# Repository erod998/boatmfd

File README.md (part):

# Boat Dashboard — Proof of Concept

A DIY Garmin-style MFD for a 7" 16:9 landscape display, restyled after the
look of Garmin's GPSMAP touchscreen chartplotters (near-black panes, round
segmented dials that fill blue, outlined data boxes, a black menu bar with a
Home button) and built for big touch targets while driving the boat.

**Moving to real hardware?** [HARDWARE.md](HARDWARE.md) has the parts list, a picked depth
transducer, and a step-by-step order to bring it up on the boat.

**Screens** (tap **Home** on the menu bar, or the small thumbnails either side
of it, to switch):

| Screen | What it shows |
| --- | --- |
| **Helm** (default) | Everything at once: GPS speed and RPM dials plus coolant / oil / battery / fuel (with estimated GPH and MPG) / trim bars on top, the chart with big Depth and Water Temp boxes in the middle, and trip, Fusion stereo and RGB lights below |
| **Nav. Chart** | Full-screen chart with Speed / Heading / Depth / Water Temp data boxes, zoom buttons, the boat, its heading line and track, an optional compass rose, and waypoint navigation |
| **Gauges** | Garmin-style engine and vessel dials: coolant, oil, battery, fuel, trim, RPM, GPS speed, fuel flow, plus fuel economy / remaining / water temp boxes |
| **Trip** | Start/stop trip logging: distance, time, average and max speed, fuel used and economy, and the saved-trip list |
| **Media** | Fusion stereo over NMEA 2000: cover art, source chips, big transport buttons, a Master volume that moves every zone together (keeping their relative mix), and a volume bar for each zone (with its own mute), plus a mute for everything, plus a gear icon for RPM Volume Boost |
| **RGB Lights** | Twelve colour presets, rainbow, power, and a segmented brightness bar |
| **Switching** | A grid of simulated digital-switching circuits (nav lights, anchor light, cabin lights, livewell, bilge pump, two accessories, horn) — no real switching module, just remembers on/off |

**Also reachable from Options** (not full screens, but full features): **Waypoints, Routes &
Boundaries** (mark/save/rename/delete waypoints, search saved waypoints by name and go straight
to one — like a GPS — build and follow multi-leg routes, circular geofence alarms), **Navigation
Alarms** (Arrival, Off Course, Anchor Drag, GPS Accuracy), and **Pinned Screens** (choose which screens
show in the Home overlay's Pinned tab and the prev/next swipe at the bottom of every screen — at
least one has to stay pinned).

**Home** is a translucent overlay like Garmin's: a clock (tap **Home** any time to check
it), a row of screen thumbnails above category tabs (Pinned, Charts, Combo, Vessel, Media,
Lights). The menu bar also has **Mark** (drop a waypoint at the boat), **Info** (data sources,
position, GPS status), **Day/Night** chart mode, **Alerts** (the alarms and
warnings below, and a missing GPS fix; the icon turns amber/red with a count)
and **Options** (units, alarms, chart orientation, map layers & colors, centre chart on
boat, waypoints, calibration). Tap the speed gauge to switch between mph and knots. The
chart defaults to **Old Hickory Lake, TN (37075)**, and has the three orientations a GPSMAP
does: **North Up** (default), **Heading Up** (the bow points to the top of the screen) and
**Course Up** (the *active leg* points to the top). Course Up is the one worth knowing about —
Heading Up re-aims the chart with every wiggle of the boat, which at idle is a constant slow
swim, while Course Up holds the leg still and lets the boat icon swing against it, so the angle
between the icon and straight-up is exactly how much you are crabbing off the track. With no Go
To or route running it falls back to course over ground, then heading, so it is never stuck
pointing somewhere stale. The chart button beside the zoom controls is labelled with the current
mode (**N↑**, **H↑**, **C↑**) and switches in one press between North Up and whichever rotating
mode you last chose; **Options → Chart orientation** cycles through all three. (It used to cycle
all three itself, and since Heading Up and Course Up look alike on a straight run, getting back
to North Up took two presses.)

**Following the boat**: the chart keeps the boat centred (North Up) or a third of the way up the
screen (Heading and Course Up) until you drag it. Then it stays where you put it, and a blue
**Center** button appears above the ruler; tap it to go back to the boat. Pinching or the +/−
buttons zoom without letting go of the boat.

**The chart cursor** — what a tap on the chart does, the way a GPSMAP does it: it drops a cursor
and does nothing else yet. The bar that appears says how far away it is and in which direction,
its position, and what is charted there (the depth band, or a bridge, dam or caution area — tap
that line for the full details); **Go To** navigates there, **Save Waypoint** keeps it. A tap used
to start a Go To immediately, and since a Go To and a route are mutually exclusive, one stray tap
in a chop cancelled an active route. Tapping an aid to navigation, mile marker, landmark or
hazard point identifies it instead, with its own Go To. Only those point features take a tap;
land, depth areas and shorelines used to as well, which between them cover the whole chart, so
every tap opened "Land" and the chart could not be tapped for anything else at all.

**Go To follows the channel** (auto guidance): a Go To is planned over the water, preferring the
Corps' recommended track down the channel, and leaves it only to reach a destination off it -- up a
creek, into a marina. The route is drawn as a dashed line and steered leg by leg: bearing, course
and cross-track error are for the current leg (so Course Up turns with the channel), distance and
time to go are along the rest of the route. With no chart or no way through the water it falls
back to a straight line and says so. Saved routes (Route To) still run straight between their
waypoints, as they do on a GPSMAP.

**Look-ahead**: in North Up the boat sits a third of the way in from the edge it is coming from,
so two thirds of the screen is the water ahead -- the bottom third heading north, the left third
heading east. It follows the course over the ground above 2 kn.

**Measure Distance** (the ruler button beside the zoom controls): the reference starts at the
boat and follows it; each tap on the chart moves the far end, and the range and bearing read out
at the top of the chart. **Set Ref** pins the reference to that point instead, to measure between
two arbitrary points; **From Boat** puts it back. (Built for a finger: an earlier version relied on
mouse hover and read 0.00 on a touchscreen.)

**Range Rings** (**Options → Map layers & colors → My Vessel**): four concentric circles around
the boat at a spacing you pick, the outermost labelled with its radius, so distance to anything
on screen can be eyeballed without measuring it. Drawn in real distance rather than screen
pixels, so they scale with zoom the way the chart does.

The boat's position and heading are eased continuously (every animation frame, not once a
second when a GPS fix arrives) — the same idea as the spring-smoothed gauges, but for a
wrapped compass angle and a lat/lon position: `setBoatTarget()`/`boatTick()` in app.js. This
drives the boat icon, the chart's own bearing in Heading Up (which turns the whole chart so
the boat's current heading points to the top of the screen, the boat icon then always
pointing straight up), and the position lock that keeps the boat horizontally centered and
about a third of the way up from the bottom of the map in Heading Up — a single cheap
`panBy` every frame, not a `setView`, so it holds through the whole rotation instead of only
correcting once a second. The chart itself is vector data held in memory (see **Charts**), so
panning and rotating never wait on anything to load and never show a blank square — the old
raster-tile black-square problem went away with the tiles.

**Map layers & colors** (**Options → Map layers & colors**, or the app/gps.py and
app/state.py simulators' more realistic noise): chart colors are Day/Dusk/Night — three real
palettes applied to the chart vectors themselves, not a filter smeared over an image, so the
boat and track keep their own colours while only the chart changes;
**Chart** layer toggles (Land & shoreline, Depths & contours, Aids to navigation, Hazards &
caution areas, Landmarks) add and remove the matching vector layers on the spot, with no
refetching — the data is already local; **My Vessel** has a Heading Line
(projects ahead of the boat by a fixed distance or by how far it'll travel in a set time at
its current speed — Distance/Time, matching a real GPSMAP's own Heading Line options) and a
Compass Rose (a fixed-size ring around the boat marked N/E/S/W — left un-rotated in CSS on
purpose, since leaflet-rotate spins the whole marker pane with the chart, the same reason the
boat icon has to counter-rotate to stay pointing up in Heading Up); **User Data** can hide the
recorded track, clear it, name and **save** the current breadcrumb trail as a permanent record
(kept in `data/tracks.json`, up to the same ~600-point/~10-minute window the live trail itself
keeps — a real chartplotter's active-track memory has the same kind of limit), and lists every
saved track — tap one to draw it on the chart in green, tap again to hide it, tap the pencil to
rename it in place, tap the arrow to drop a waypoint back at its starting point (retracing it, the
way you'd want to find your way back to the dock after an out-and-back cruise), or delete it. All
of this is a per-browser preference (localStorage) except clearing the track, and saved tracks
themselves, which live on the server (`/api/track`, `/api/tracks`).

**Data overlays** (the Speed/Heading/Depth/... boxes on the Helm and Nav. Chart screens): **hold**
any box (same gesture, and the same fill-as-you-hold feedback, as the RPM display and alarm
menus) to swap in a different field, matching a real GPSMAP's "Edit Overlays". There are **36
fields in seven groups**, and the picker shows the group headings because a flat list of that
many is not something anyone navigates while driving:

| Group | Fields |
| --- | --- |
| **Navigation** | Bearing, Course, Distance, Time To Dest, Arrival Time, VMG, Cross Track, Turn, Destination |
| **Vessel** | Speed, Heading, Course Over Ground, Position, GPS Accuracy, Satellites |
| **Depth & Water** | Depth, Water Temp |
| **Engine** | RPM, Engine Temp, Oil Pressure, Trim, Battery |
| **Fuel** | Fuel Level, Fuel Remaining, Fuel Rate, Fuel Economy, Range |
| **Trip** | Trip Distance, Trip Time, Average Speed, Max Speed, Trip Fuel Used |
| **Time** | Time of Day, Sunrise, Sunset, Moon Phase |

The Navigation group needs a Go To or a route running and reads `--` otherwise, the Trip group
needs a trip started, and everything reads `--` without a GPS fix — which is what a real unit
does rather than showing a stale or invented number. **VMG** is velocity made good: how fast the
distance to the destination is actually shrinking, which is only the same as speed when steering
straight at it. **Time To Dest** is computed from VMG rather than speed for exactly that reason
— sliding sideways past a waypoint at 20 kn is not arriving at 20 kn — and reads `--` when VMG
has gone negative, because a boat pointed away is not arriving at all. **Fuel Remaining**,
**Economy** and **Range** need the tank size (`BOAT_FUEL_CAPACITY_GAL`, default 40).
Which fields are picked, per screen, is a per-browser preference (localStorage);
the Chart screen defaults to Speed/Heading/Depth/Water Temp and the Helm screen (which already
shows speed via its own dial) to Depth/Water Temp, same as before this was made editable.
Sunrise, sunset and moon phase come from `app/celestial.py` — sunrise/sunset from the standard
astronomical "sunrise equation" using the boat's own position, moon phase from the days elapsed
since a known new moon (the same for every observer, so it only needs a date) — both accurate to
civil (not celestial-navigation) precision, no network call or API key, and (deliberately) not
tide/current predictions or moonrise/moonset times, which either wouldn't mean anything on a
freshwater lake (tide/current) or need meaningfully more work to compute well (the moon's real
position, not just its phase angle) than this dashboard's use case calls for.

**Alarms:** hold your finger on a gauge for about half a second (the gauge
fills as you hold) to open its alarm menu: coolant / engine temperature, oil
pressure, battery voltage (a low and a high alarm), fuel level, or the Depth
box. **Options → Alarms** lists them all. Each has an on/off switch and a
level you set with the big −/+ buttons or by tapping the bar; a small bell
marks every gauge that has an alarm on, and the gauge's red and amber bands
move to match the level. Coolant and engine temperature are the same reading
here (one engine-temperature gauge). Details are in "Alarms" below.

**Waypoints, Routes & Boundaries** (**Options → Waypoints, Routes & Boundaries**): mark the
boat's current position as a named, saved waypoint (separate from the single "Go To" target the
chart cursor sets); go to one, rename it in place, or delete it. Build a **route** by
checking two or more saved waypoints in the order you want to visit them — following one steers
leg to leg and auto-advances to the next point on arrival (within ~300 ft), the same way a single
Go To does, and the two are mutually exclusive (starting a route stops a Go To and vice versa).
**Boundaries** are a circular geofence around a point — pick a radius and whether the alarm fires
on entering, exiting, or both — for a no-wake zone, a marina, water you want a heads-up about
either way. Only circles, not the arbitrary polygons a real Garmin supports: a circle is a tap
and a radius, a polygon needs collecting an ordered ring of points on a touchscreen, and circles
already cover "stay near/away from this spot."

**Navigation Alarms** (**Options → Navigation Alarms**): **Arrival** (nearing the active
waypoint or route leg, on by default), **Off Course** (strayed too far from the direct line, by
cross-track error), **GPS Accuracy** (the fix's own reported HDOP has gotten too poor to trust),
and **Anchor Drag** — drop a reference point at the current position and get alarmed if the boat
drifts past a set radius from it, checked against the real (or simulated) GPS fix every second,
the same way a real chartplotter's anchor watch works. All four, plus boundary crossings, show up
in the same Alerts panel and banner as the engine/boat alarms; unlike those, they don't have an
"acknowledge" — they clear on their own once the condition does (back on course, anchor
re-settled), except a boundary crossing, which is a one-time event held in the alert list for 8
seconds so it doesn't disappear before the once-a-second Alerts badge or banner even shows it.

**Digital Switching** (the **Switching** screen): eight named on/off circuits (nav lights, anchor
light, cabin lights, livewell, bilge pump, two accessories, horn) standing in for a real NMEA
2000 digital-switching module (a CZone/Empirbus-style relay box) — there isn't one wired up, so
each circuit just remembers its own state, the same simulate-what-there's-no-hardware-for
approach as the rest of this dashboard.

**Smooth gauges:** engine and boat readings arrive five times a second (GPS,
trip, stereo and lights once a second), and every dial, bar and number glides
to each new reading on a critically damped spring instead of jumping, so
needles start and stop gently and never overshoot. How quickly a needle
follows a new reading is itself adjustable: hold either RPM gauge (Helm or
Gauges screen) to open "Engine RPM display" and pick from Very smooth to
Snappy — useful once a real, noisier tach signal replaces the simulator's.
No amount of easing can fully hide noise with a genuinely slow, drifting
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
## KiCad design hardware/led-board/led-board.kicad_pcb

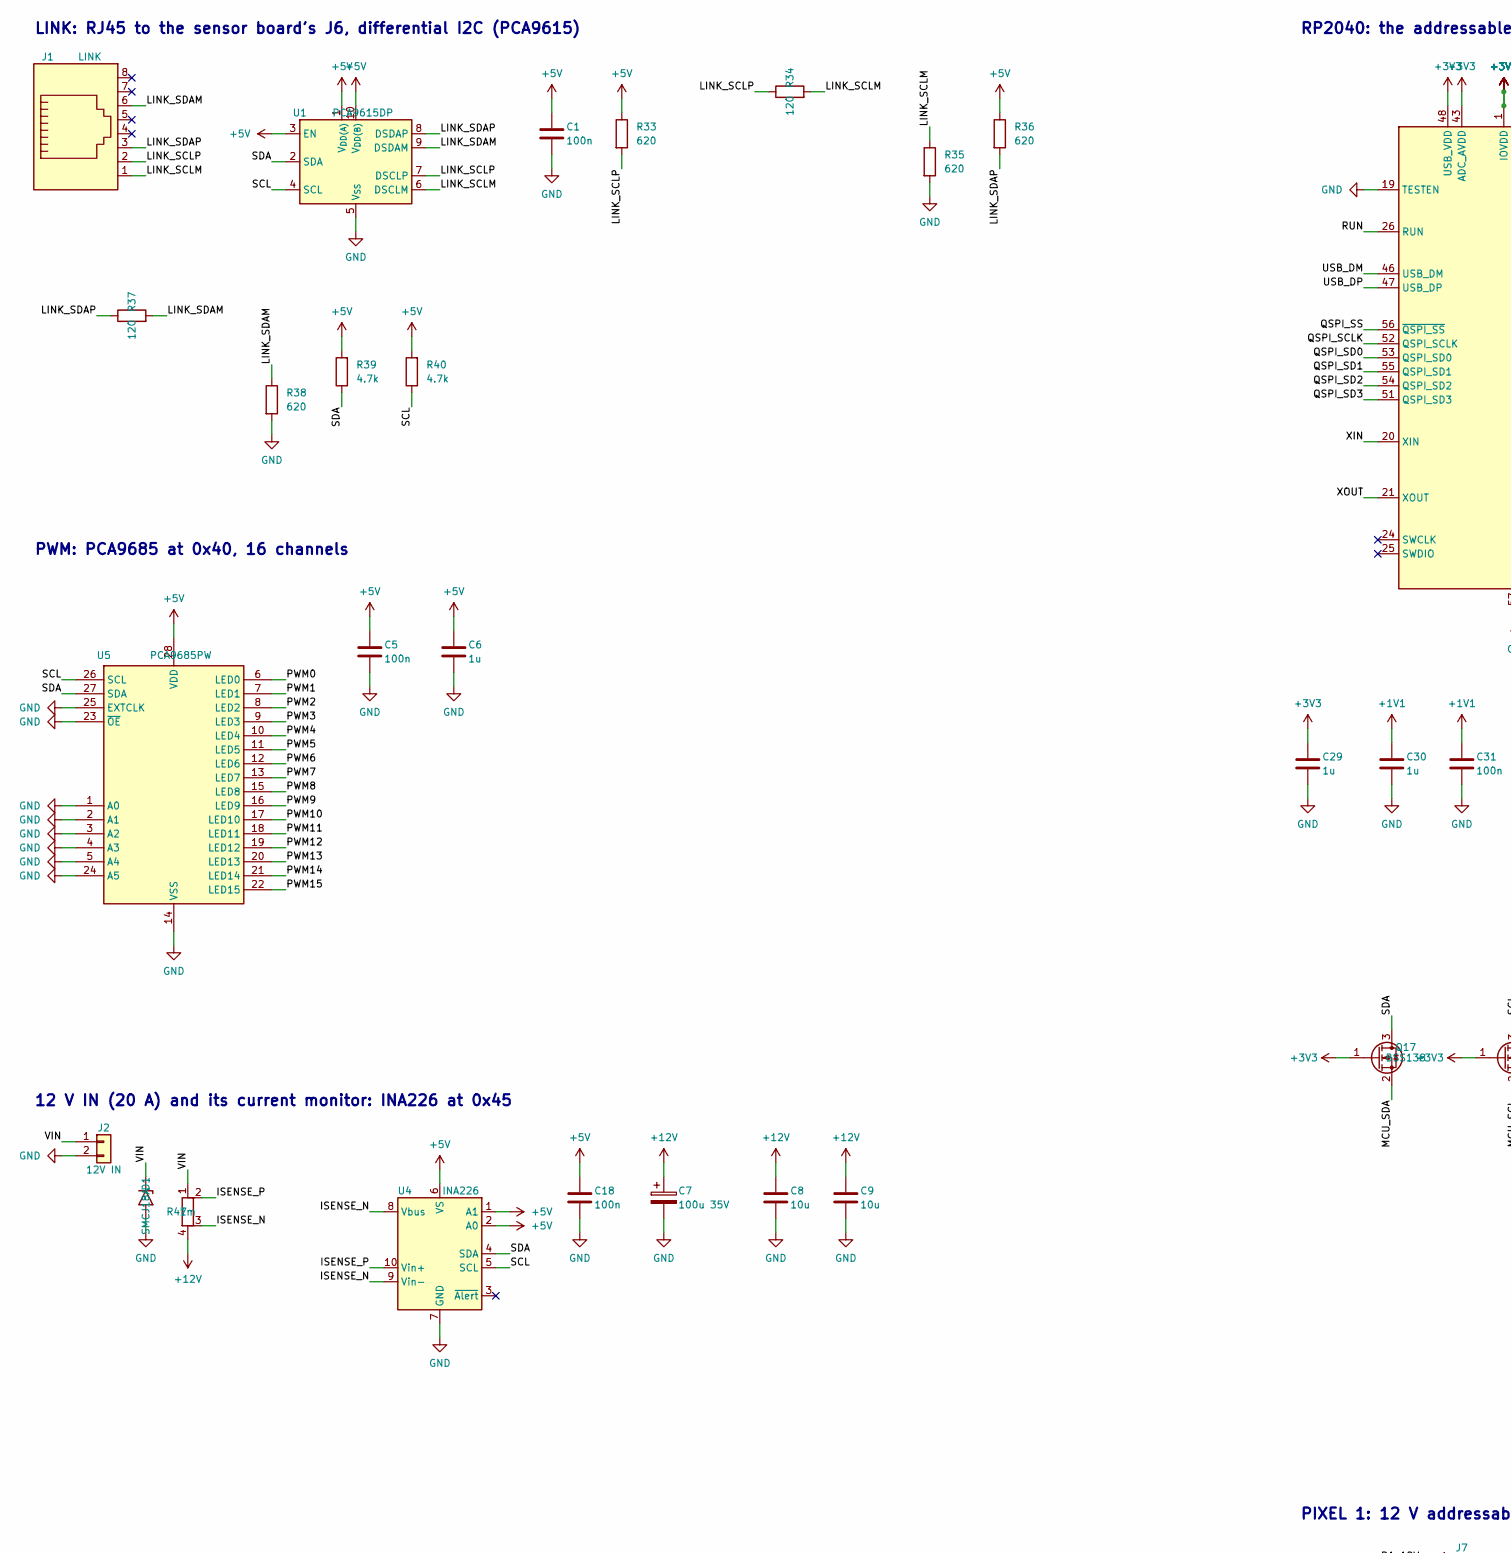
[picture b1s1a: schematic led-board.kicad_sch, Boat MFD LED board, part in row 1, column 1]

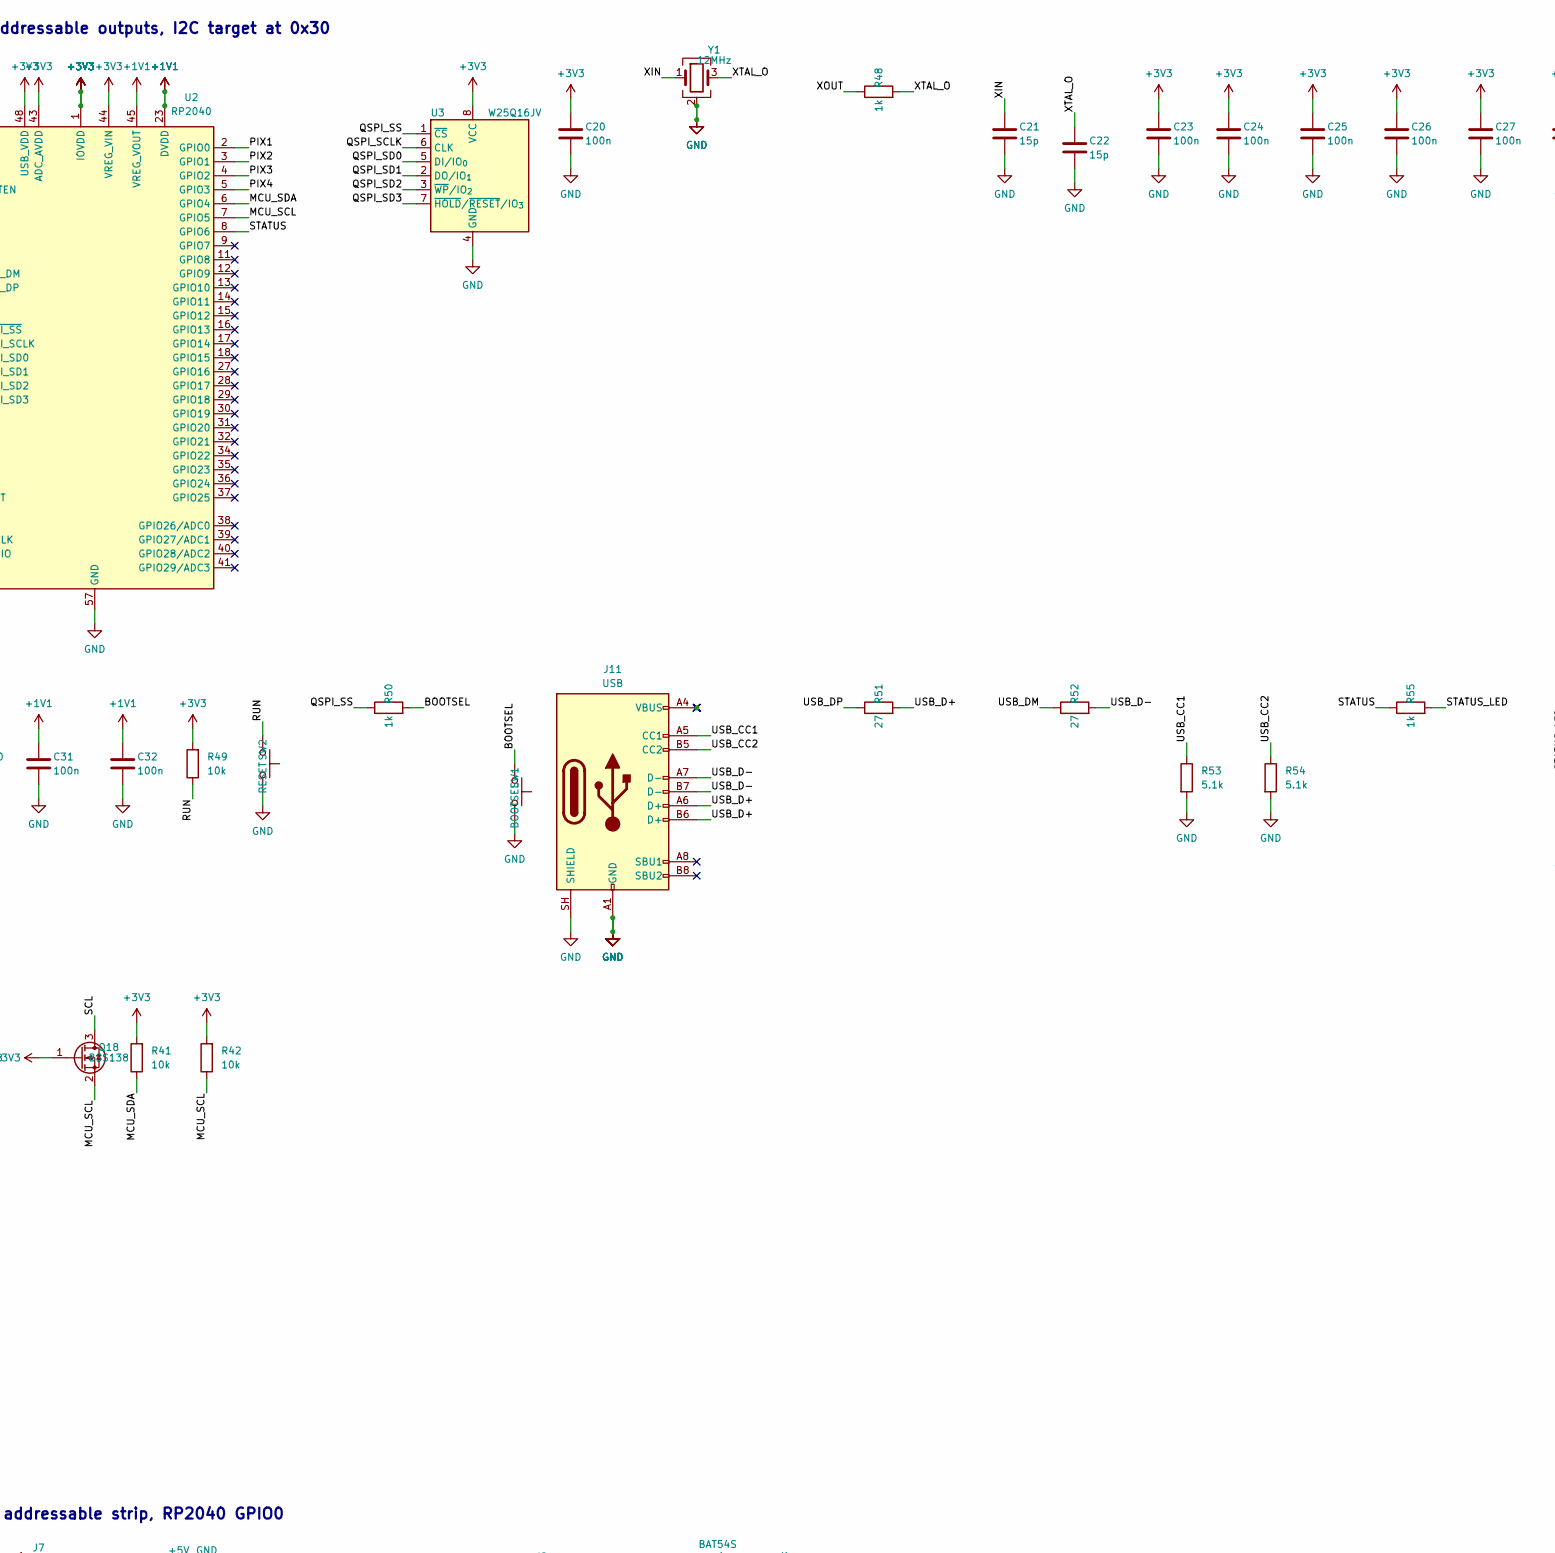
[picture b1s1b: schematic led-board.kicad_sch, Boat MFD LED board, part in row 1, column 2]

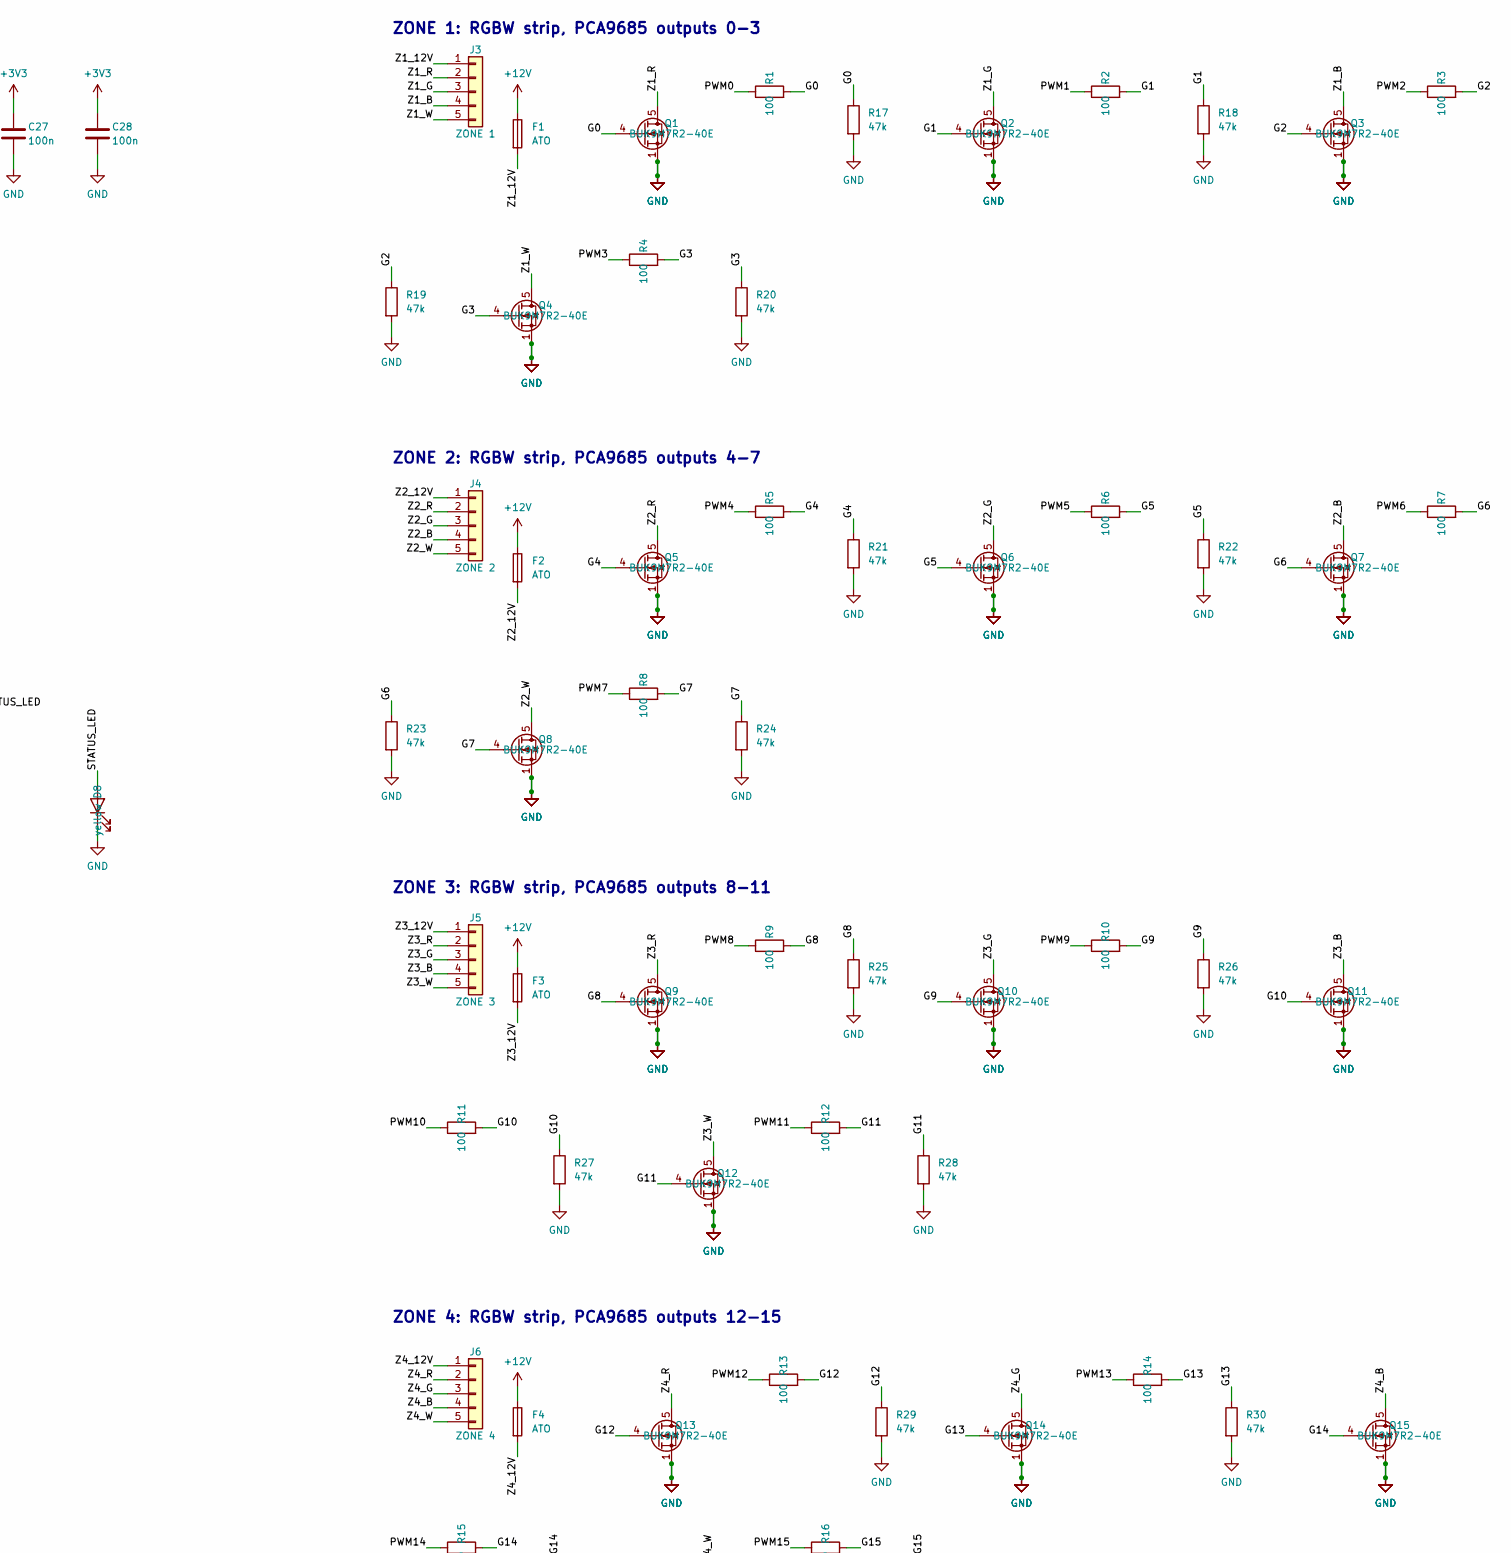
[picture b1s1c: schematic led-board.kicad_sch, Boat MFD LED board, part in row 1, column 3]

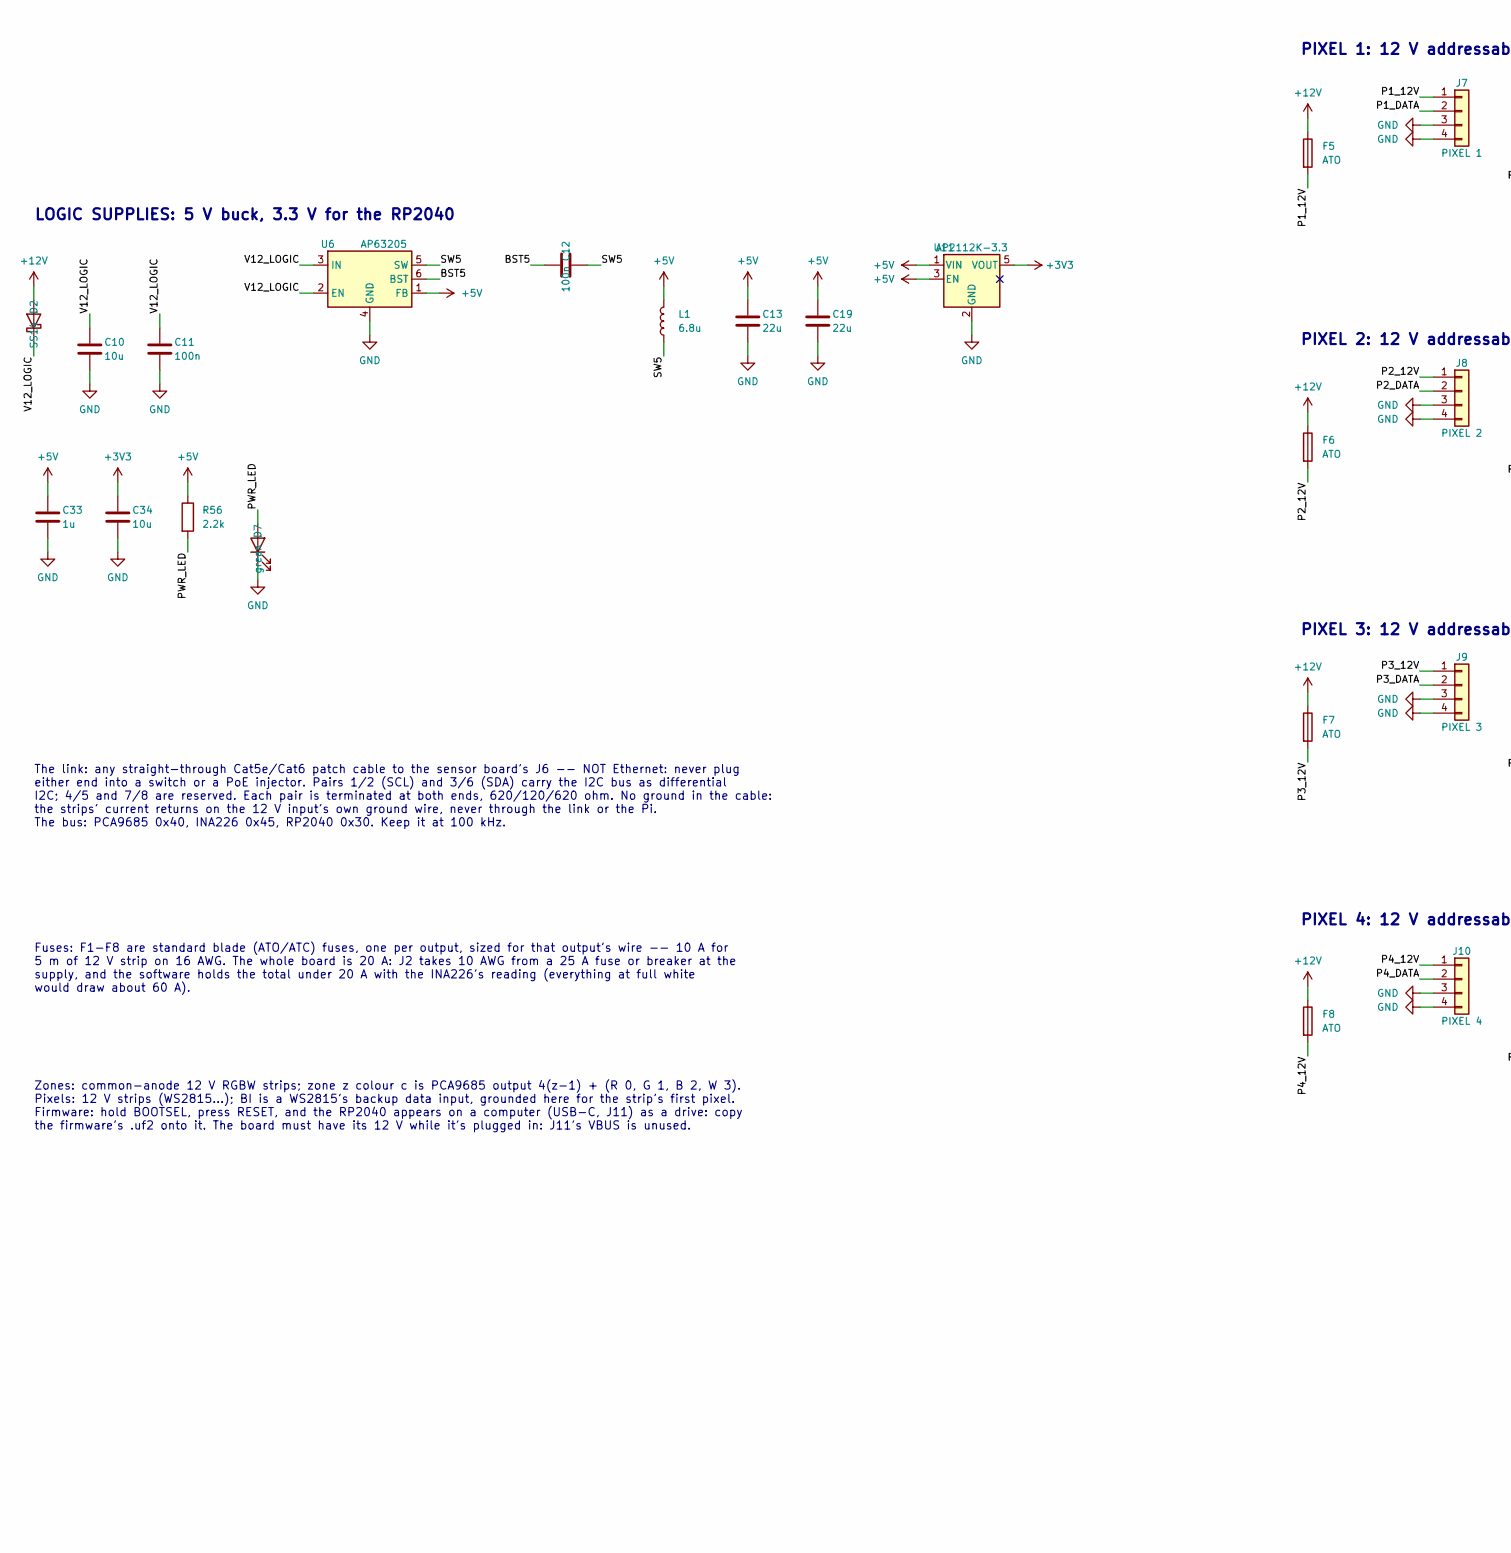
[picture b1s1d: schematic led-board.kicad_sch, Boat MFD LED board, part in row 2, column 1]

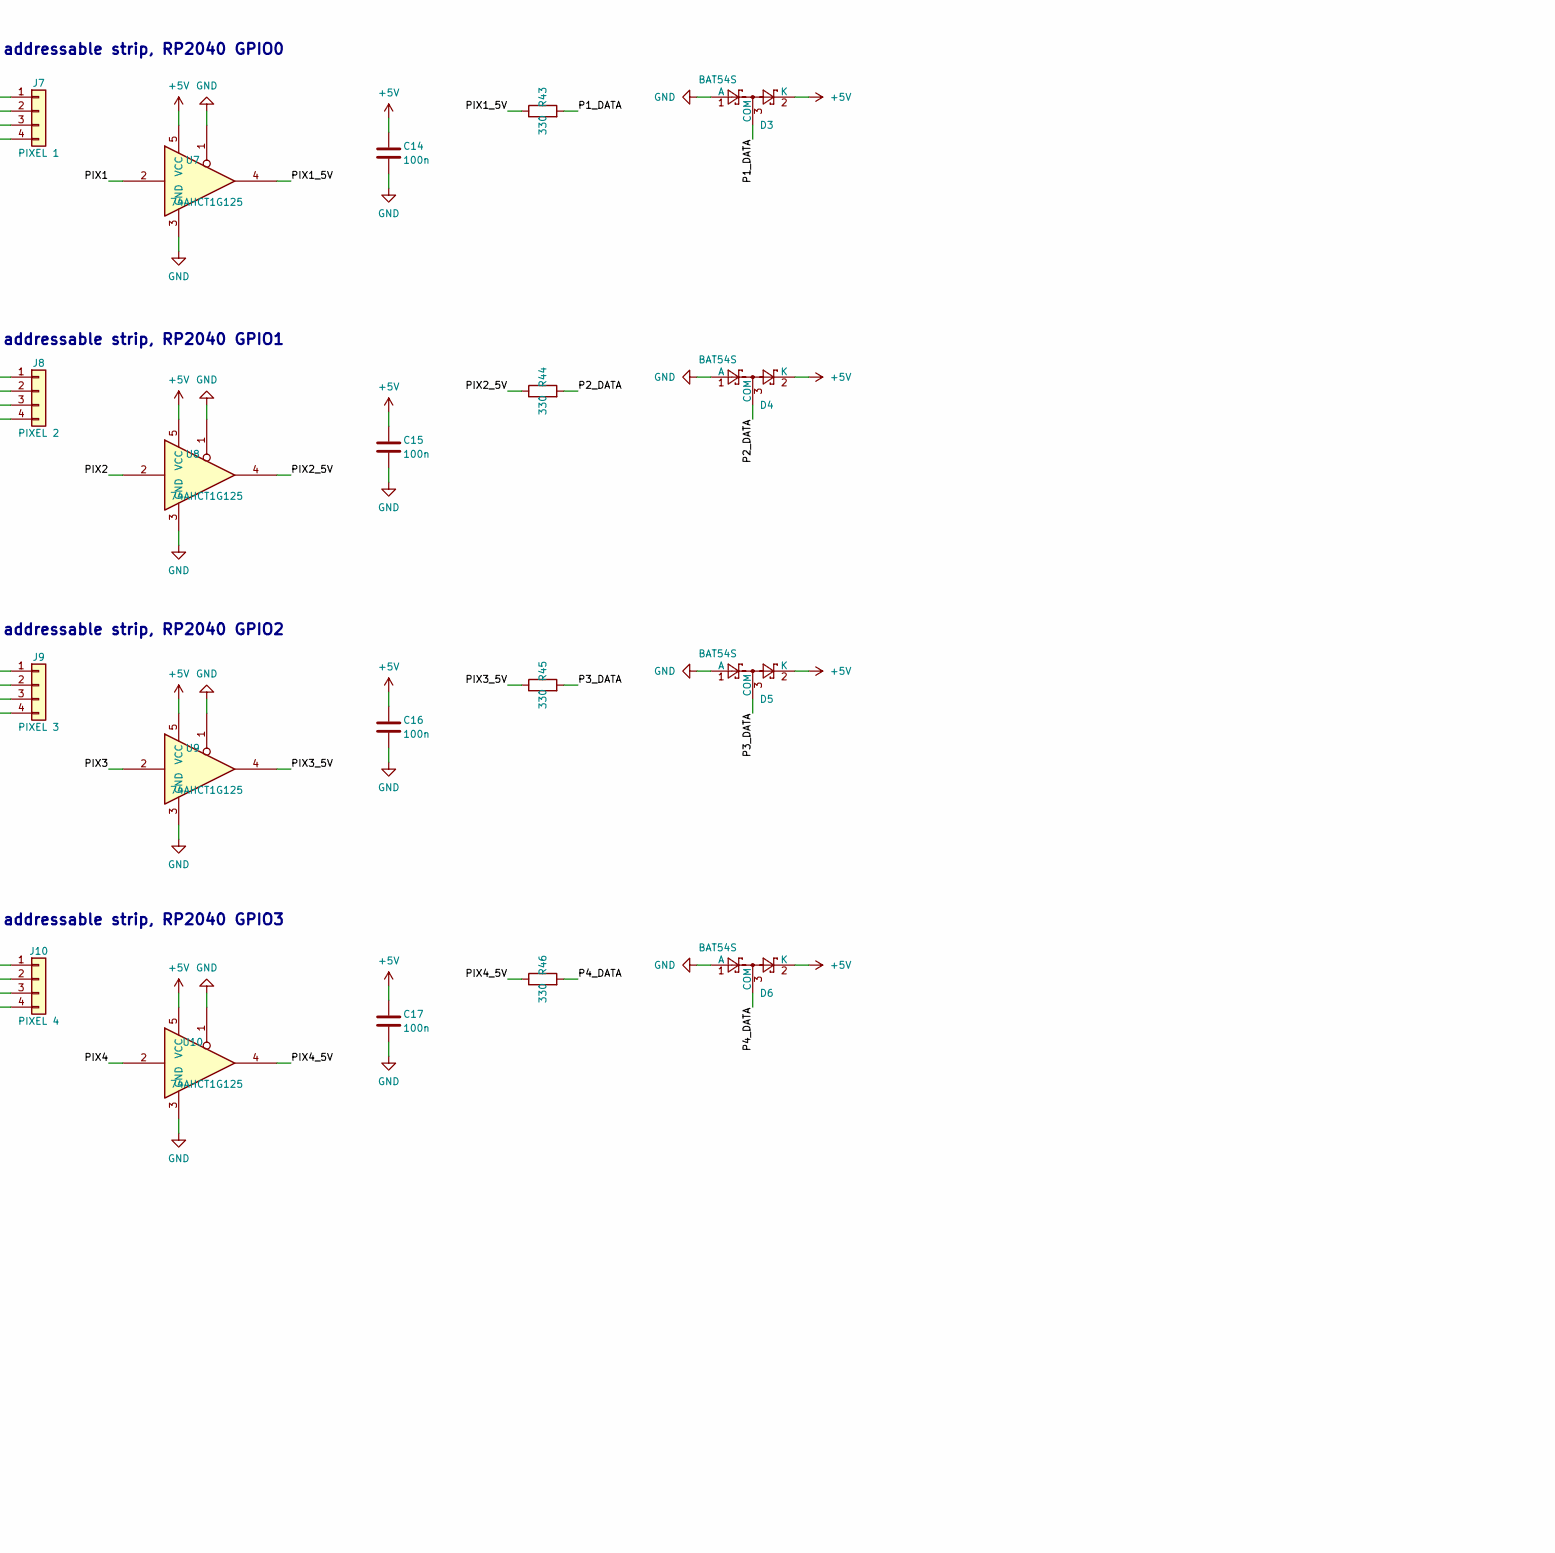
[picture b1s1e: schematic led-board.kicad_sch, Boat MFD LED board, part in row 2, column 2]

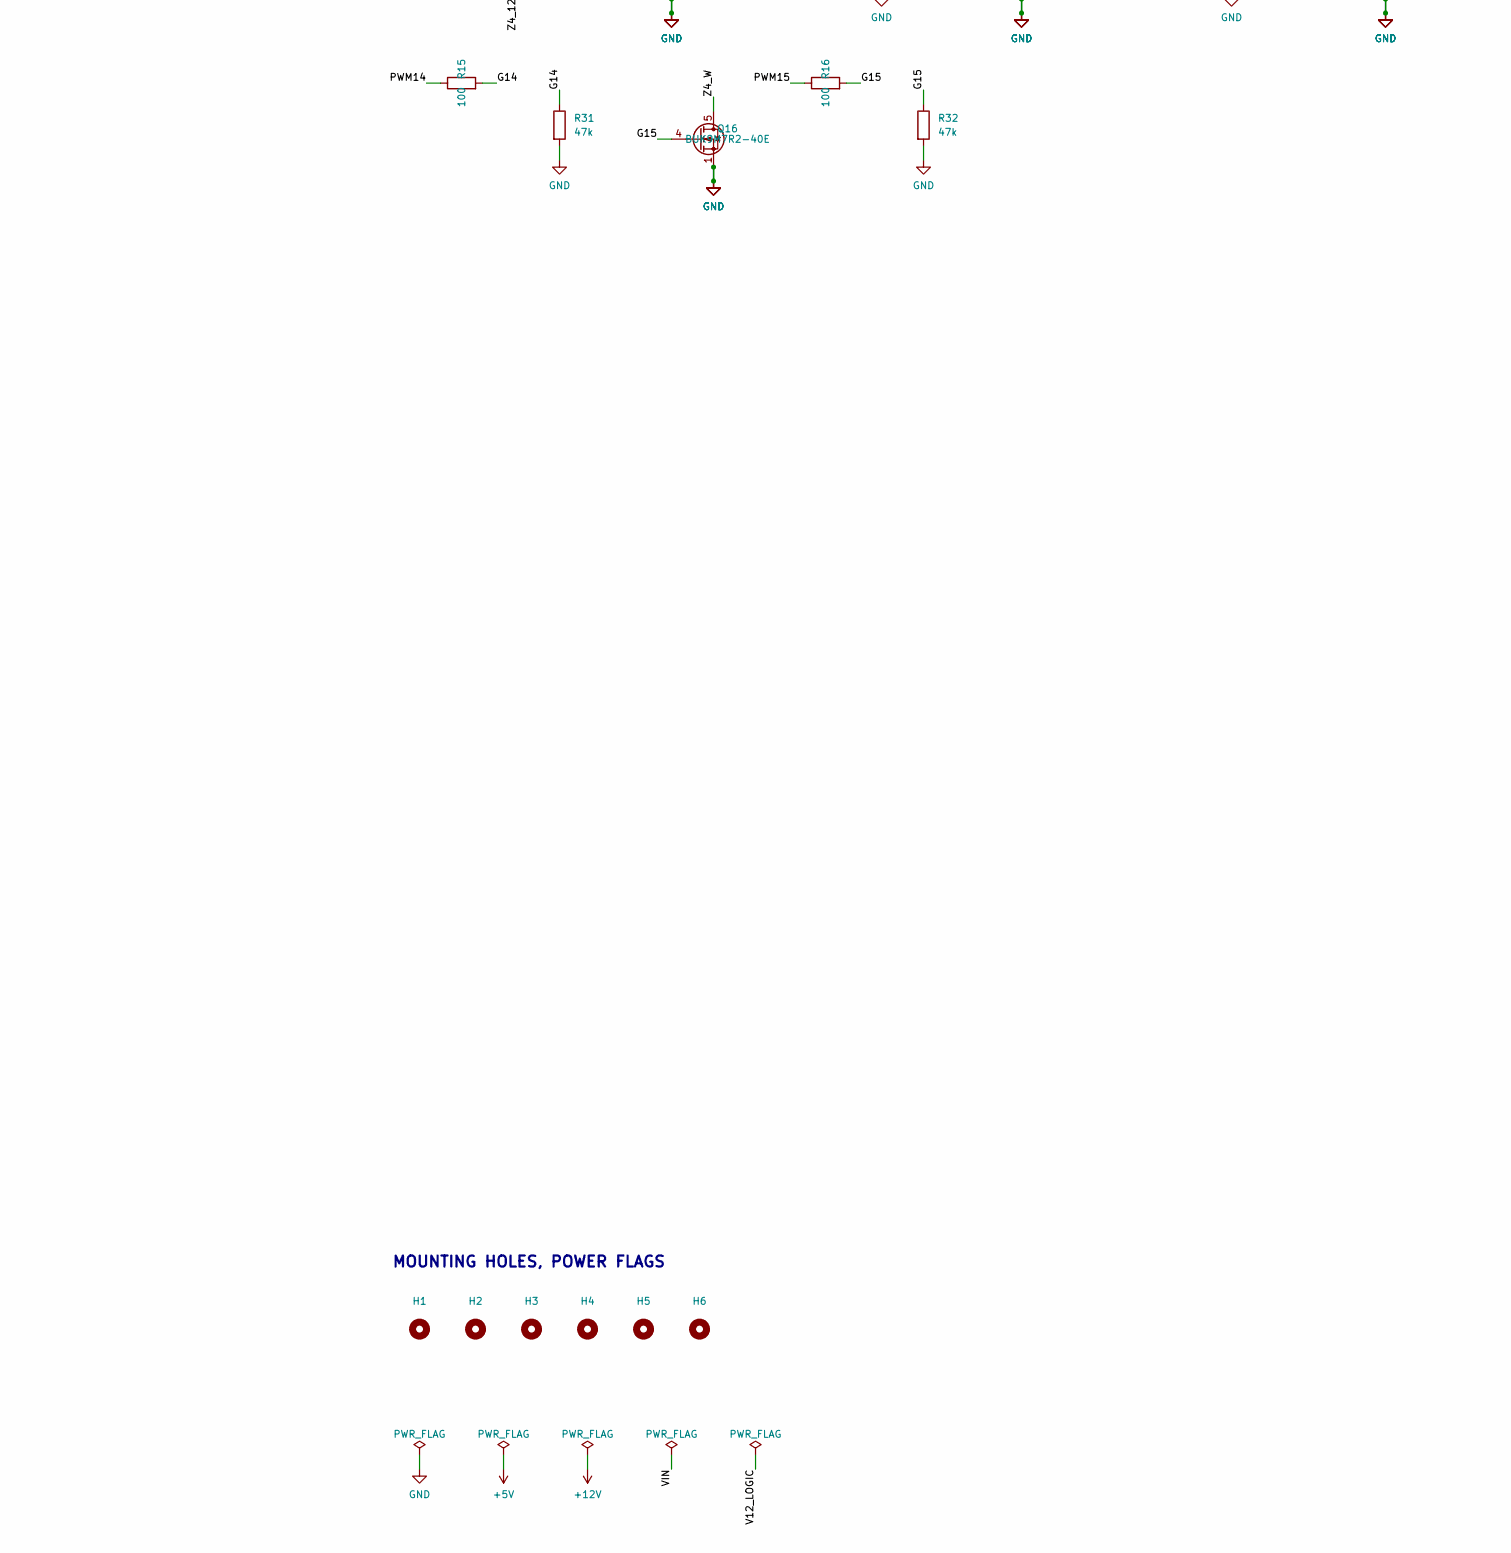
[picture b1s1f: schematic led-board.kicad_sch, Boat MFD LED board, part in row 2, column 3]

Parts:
C1, C5, C11, C12, C14, C15, C16, C17, C18: 100n; C_0805_2012Metric_NoSilk; MPN CL21B104KBCNNNC
C6, C33: 1u; C_0805_2012Metric_NoSilk; MPN CL21B105KAFNNNE
C7: 100u 35V; CP_Elec_8x10; MPN EEE-FK1V101P
C8, C9, C10: 10u; C_1210_3225Metric; MPN CL32B106KBJNNNE
C13, C19: 22u; C_1206_3216Metric_NoSilk; MPN CL31A226KAHNNNE
C20, C23, C24, C25, C26, C27, C28, C31, C32: 100n; C_0402_1005Metric_NoSilk; MPN CL05B104KO5NNNC
C21, C22: 15p; C_0402_1005Metric_NoSilk; MPN CL05C150JB5NNNC
C29, C30: 1u; C_0402_1005Metric_NoSilk; MPN CL05A105KA5NQNC
C34: 10u; C_0805_2012Metric_NoSilk; MPN CL21A106KAYNNNE
D1: SMCJ18A; D_SMC; MPN SMCJ18A
D2: SS14; D_SMA; MPN SS14
D3, D4, D5, D6: BAT54S; SOT-23_NoSilk; MPN BAT54S,215
D7: green; LED_0805_2012Metric; MPN LTST-C171GKT
D8: yellow; LED_0805_2012Metric; MPN LTST-C171YKT
F1, F2, F3, F4, F5, F6, F7, F8: ATO; FuseHolder_Blade_ATO_Littelfuse_FLR_178.6165; MPN Littelfuse 178.6165.0002 (ATO/ATC holde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
H1, H2, H3, H4, H5, H6: MountingHole; MountingHole_3.2mm_M3
J1: LINK; RJ45_Amphenol_54602-x08_Horizontal; MPN Amphenol 54602-908LF
J2: 12V IN; TerminalBlock_MetzConnect_Type703_RT10N02HGLU_1x02_P9.52mm_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; MPN METZ CONNECT RT10N02HGLU
J3: ZONE 1; PhoenixContact_MSTB_2,5_5-GF-5,08_1x05_P5.08mm_Horizontal_T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; MPN Phoenix Contact 1776537 (MSTB 2,5/ 5-GF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
J4: ZONE 2; PhoenixContact_MSTB_2,5_5-GF-5,08_1x05_P5.08mm_Horizontal_T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; MPN Phoenix Contact 1776537 (MSTB 2,5/ 5-GF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
J5: ZONE 3; PhoenixContact_MSTB_2,5_5-GF-5,08_1x05_P5.08mm_Horizontal_T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; MPN Phoenix Contact 1776537 (MSTB 2,5/ 5-GF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
J6: ZONE 4; PhoenixContact_MSTB_2,5_5-GF-5,08_1x05_P5.08mm_Horizontal_T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; MPN Phoenix Contact 1776537 (MSTB 2,5/ 5-GF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
J7: PIXEL 1; PhoenixContact_MSTB_2,5_4-GF-5,08_1x04_P5.08mm_Horizontal_T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; MPN Phoenix Contact 1776524 (MSTB 2,5/ 4-GF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
J8: PIXEL 2; PhoenixContact_MSTB_2,5_4-GF-5,08_1x04_P5.08mm_Horizontal_T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; MPN Phoenix Contact 1776524 (MSTB 2,5/ 4-GF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
J9: PIXEL 3; PhoenixContact_MSTB_2,5_4-GF-5,08_1x04_P5.08mm_Horizontal_T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; MPN Phoenix Contact 1776524 (MSTB 2,5/ 4-GF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
J10: PIXEL 4; PhoenixContact_MSTB_2,5_4-GF-5,08_1x04_P5.08mm_Horizontal_T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; MPN Phoenix Contact 1776524 (MSTB 2,5/ 4-GF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
J11: USB; USB_C_Receptacle_GCT_USB4105-xx-A_16P_TopMnt_Horizontal; MPN GCT USB4105-GF-A
L1: 6.8u; L_Bourns_SRN6045TA; MPN SRN6045TA-6R8M
Q1, Q2, Q3, Q4, Q5, Q6, Q7, Q8, Q9, Q10, Q11, Q12, Q13, Q14, Q15, Q16: BUK9M7R2-40E; LFPAK33; MPN BUK9M7R2-40EX
Q17, Q18: BSS138; SOT-23; MPN BSS138
R1, R2, R3, R4, R5, R6, R7, R8, R9, R10, R11, R12, R13, R14, R15, R16: 100; R_0805_2012Metric_NoSilk; MPN RC0805FR-07100RL
R17, R18, R19, R20, R21, R22, R23, R24, R25, R26, R27, R28, R29, R30, R31, R32: 47k; R_0805_2012Metric_NoSilk; MPN RC0805FR-0747KL
R33, R35, R36, R38: 620; R_0805_2012Metric_NoSilk; MPN RC0805FR-07620RL
R34, R37: 120; R_0805_2012Metric_NoSilk; MPN RC0805FR-07120RL
R39, R40: 4.7k; R_0805_2012Metric_NoSilk; MPN RC0805FR-074K7L
R41, R42, R49: 10k; R_0805_2012Metric_NoSilk; MPN RC0805FR-0710KL
R43, R44, R45, R46: 330; R_1206_3216Metric_NoSilk; MPN RC1206FR-07330RL
R47: 1m; R_Shunt_Vishay_WSK2512_6332Metric_T2.21mm; MPN WSK25121L000FEA
R48: 1k; R_0402_1005Metric_NoSilk; MPN RC0402FR-071KL
R50, R55: 1k; R_0805_2012Metric_NoSilk; MPN RC0805FR-071KL
R51, R52: 27; R_0402_1005Metric_NoSilk; MPN RC0402FR-0727RL
R53, R54: 5.1k; R_0805_2012Metric_NoSilk; MPN RC0805FR-075K1L
R56: 2.2k; R_0805_2012Metric_NoSilk; MPN RC0805FR-072K2L
SW1: BOOTSEL; SW_Push_1P1T_NO_CK_KMR2; MPN KMR221GLFS
SW2: RESET; SW_Push_1P1T_NO_CK_KMR2; MPN KMR221GLFS
U1: PCA9615DP; TSSOP-10_3x3mm_P0.5mm; MPN PCA9615DP,118
U2: RP2040; QFN-56-1EP_7x7mm_P0.4mm_EP3.2x3.2mm_ThermalVias_Drill0.3; MPN RP2040
U3: W25Q16JV; SOIC-8_5.3x5.3mm_P1.27mm; MPN W25Q16JVSSIQ
U4: INA226; TSSOP-10_3x3mm_P0.5mm; MPN INA226AIDGSR
U5: PCA9685PW; TSSOP-28_4.4x9.7mm_P0.65mm; MPN PCA9685PW,118
U6: AP63205; TSOT-23-6; MPN AP63205WU-7
U7, U8, U9, U10: 74AHCT1G125; SOT-23-5; MPN SN74AHCT1G125DBVR
U11: AP2112K-3.3; SOT-23-5; MPN AP2112K-3.3TRG1
Y1: 12MHz; Crystal_SMD_3225-4Pin_3.2x2.5mm; MPN ABM8-272-T3

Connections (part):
+1V1: C30.1, C31.1, C32.1, U2.23 (DVDD), U2.45 (VREG_VOUT), U2.50 (DVDD)
+3V3: C20.1, C23.1, C24.1, C25.1, C26.1, C27.1, C28.1, C29.1, C34.1, Q17.1 (G), Q18.1 (G), R41.2, R42.2, R49.2, U2.1 (IOVDD), U2.10 (IOVDD), U2.22 (IOVDD), U2.33 (IOVDD), U2.42 (IOVDD), U2.43 (ADC_AVDD), U2.44 (VREG_VIN), U2.48 (USB_VDD), U2.49 (IOVDD), U3.8 (VCC), U11.5 (VOUT)
+5V: C1.1, C5.1, C6.1, C13.1, C14.1, C15.1, C16.1, C17.1, C18.1, C19.1, C33.1, D3.2 (K), D4.2 (K), D5.2 (K), D6.2 (K), L1.2, R33.1, R36.1, R39.2, R40.2, R56.1, U1.1 (V_{DD(A)}), U1.3 (EN), U1.10 (V_{DD(B)}), U4.1 (A1), U4.2 (A0), U4.6 (VS), U5.28 (VDD), U6.1 (FB), U7.5 (VCC), U8.5 (VCC), U9.5 (VCC), U10.5 (VCC), U11.1 (VIN), U11.3 (EN)
+12V: C7.1, C8.1, C9.1, D2.2 (A), F1.1, F2.1, F3.1, F4.1, F5.1, F6.1, F7.1, F8.1, R47.4
/BOOTSEL: R50.2, SW1.1
/BST5: C12.1, U6.6 (BST)
/G0: Q1.4 (G), R1.2, R17.1
/G1: Q2.4 (G), R2.2, R18.1
/G2: Q3.4 (G), R3.2, R19.1
/G3: Q4.4 (G), R4.2, R20.1
/G4: Q5.4 (G), R5.2, R21.1
/G5: Q6.4 (G), R6.2, R22.1
/G6: Q7.4 (G), R7.2, R23.1
/G7: Q8.4 (G), R8.2, R24.1
/G8: Q9.4 (G), R9.2, R25.1
/G9: Q10.4 (G), R10.2, R26.1
/G10: Q11.4 (G), R11.2, R27.1
/G11: Q12.4 (G), R12.2, R28.1
/G12: Q13.4 (G), R13.2, R29.1
/G13: Q14.4 (G), R14.2, R30.1
/G14: Q15.4 (G), R15.2, R31.1
/G15: Q16.4 (G), R16.2, R32.1
/ISENSE_N: R47.3, U4.8 (Vbus), U4.9 (Vin-)
/ISENSE_P: R47.2, U4.10 (Vin+)
/LINK_SCLM: J1.1, R34.2, R35.1, U1.6 (DSCLM)
/LINK_SCLP: J1.2, R33.2, R34.1, U1.7 (DSCLP)
/LINK_SDAM: J1.6, R37.2, R38.1, U1.9 (DSDAM)
/LINK_SDAP: J1.3, R36.2, R37.1, U1.8 (DSDAP)
/MCU_SCL: Q18.2 (S), R42.1, U2.7 (GPIO5)
/MCU_SDA: Q17.2 (S), R41.1, U2.6 (GPIO4)
/P1_12V: F5.2, J7.1
/P1_DATA: D3.3 (COM), J7.2, R43.2
/P2_12V: F6.2, J8.1
/P2_DATA: D4.3 (COM), J8.2, R44.2
/P3_12V: F7.2, J9.1
/P3_DATA: D5.3 (COM), J9.2, R45.2
/P4_12V: F8.2, J10.1
/P4_DATA: D6.3 (COM), J10.2, R46.2
/PIX1: U2.2 (GPIO0), U7.2
/PIX1_5V: R43.1, U7.4
/PIX2: U2.3 (GPIO1), U8.2
/PIX2_5V: R44.1, U8.4
/PIX3: U2.4 (GPIO2), U9.2
/PIX3_5V: R45.1, U9.4
/PIX4: U2.5 (GPIO3), U10.2
/PIX4_5V: R46.1, U10.4
/PWM0: R1.1, U5.6 (LED0)
/PWM1: R2.1, U5.7 (LED1)
/PWM2: R3.1, U5.8 (LED2)
/PWM3: R4.1, U5.9 (LED3)
/PWM4: R5.1, U5.10 (LED4)
/PWM5: R6.1, U5.11 (LED5)
/PWM6: R7.1, U5.12 (LED6)
/PWM7: R8.1, U5.13 (LED7)
/PWM8: R9.1, U5.15 (LED8)
/PWM9: R10.1, U5.16 (LED9)
/PWM10: R11.1, U5.17 (LED10)
/PWM11: R12.1, U5.18 (LED11)
/PWM12: R13.1, U5.19 (LED12)
/PWM13: R14.1, U5.20 (LED13)
/PWM14: R15.1, U5.21 (LED14)
/PWM15: R16.1, U5.22 (LED15)
/PWR_LED: D7.2 (A), R56.2
/QSPI_SCLK: U2.52 (QSPI_SCLK), U3.6 (CLK)
/QSPI_SD0: U2.53 (QSPI_SD0), U3.5 (DI/IO_{0})
/QSPI_SD1: U2.55 (QSPI_SD1), U3.2 (DO/IO_{1})
/QSPI_SD2: U2.54 (QSPI_SD2), U3.3 (~WP/IO_{2})
/QSPI_SD3: U2.51 (QSPI_SD3), U3.7 (~HOLD/~RESET/IO_{3})
/QSPI_SS: R50.1, U2.56 (~QSPI_SS), U3.1 (~CS)
/RUN: R49.1, SW2.1, U2.26 (RUN)
/SCL: Q18.3 (D), R40.1, U1.4 (SCL), U4.5 (SCL), U5.26 (SCL)
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
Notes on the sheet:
LINK: RJ45 to the sensor board's J6, differential I2C (PCA9615)
PWM: PCA9685 at 0x40, 16 channels
12 V IN (20 A) and its current monitor: INA226 at 0x45
LOGIC SUPPLIES: 5 V buck, 3.3 V for the RP2040
RP2040: the addressable outputs, I2C target at 0x30
ZONE 1: RGBW strip, PCA9685 outputs 0-3
ZONE 2: RGBW strip, PCA9685 outputs 4-7
ZONE 3: RGBW strip, PCA9685 outputs 8-11
ZONE 4: RGBW strip, PCA9685 outputs 12-15
PIXEL 1: 12 V addressable strip, RP2040 GPIO0
PIXEL 2: 12 V addressable strip, RP2040 GPIO1
PIXEL 3: 12 V addressable strip, RP2040 GPIO2
PIXEL 4: 12 V addressable strip, RP2040 GPIO3
MOUNTING HOLES, POWER FLAGS
The link: any straight-through Cat5e/Cat6 patch cable to the sensor board's J6 -- NOT Ethernet: never plug either end into a switch or a PoE injector. Pairs 1/2 (SCL) and 3/6 (SDA) carry the I2C bus as differential I2C; 4/5 and 7/8 are reserved. Each pair is terminated at both ends, 620/120/620 ohm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
Fuses: F1-F8 are standard blade (ATO/ATC) fuses, one per output, sized for that output's wire -- 10 A for 5 m of 12 V strip on 16 AWG. The whole board is 20 A: J2 takes 10 AWG from a 25 A fuse or breaker at the supply, and the software holds the total under 20 A with the INA226's reading (everythin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
Zones: common-anode 12 V RGBW strips; zone z colour c is PCA9685 output 4(z-1) + (R 0, G 1, B 2, W 3). Pixels: 12 V strips (WS2815...); BI is a WS2815's backup data input, grounded here for the strip's first pixel. Firmware: hold BOOTSEL, press RESET, and the RP2040 appears on a computer (USB-C, J1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
